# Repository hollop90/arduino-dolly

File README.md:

# Arduino Dolly

A clone of the Arduino Nano, but a little different.

## Overview Image

## Schematic

## 3D PCB

## Copper Layers

## todos

- [X] calculate crystal values
  - [X] calculate load capacitors - 12pf
  - [X] inspect layout - seems fine
- [X] Research USB TVS diodes
  - [X] the ones i'm using are probably not appropriate - yeah they are for RS485. FIXED
  - [X] look into what phils lab uses or the CATS board
- [X] Look into controlled impedance traces. NOT NEEDED
  - [X] calculate for the USB port. NOT DONE
- [X] Double check USB C layout
  - [X] ground the shilding
  - [X] series termination reistors? NAH
- [X] double check vreg capacitors. NEXT TIME USE 10u ON BOTH SIDES
- [X] check all capacitor dielectrics
- [X] add a fuse?. NO
- [X] review voltage selector diode. LGTM
- [X] Make a final BOM
- [X] Make production files
- [ ] Rip up traces and try alternete routing for MCU
- [X] CP2102 and others, what to do with unused pins

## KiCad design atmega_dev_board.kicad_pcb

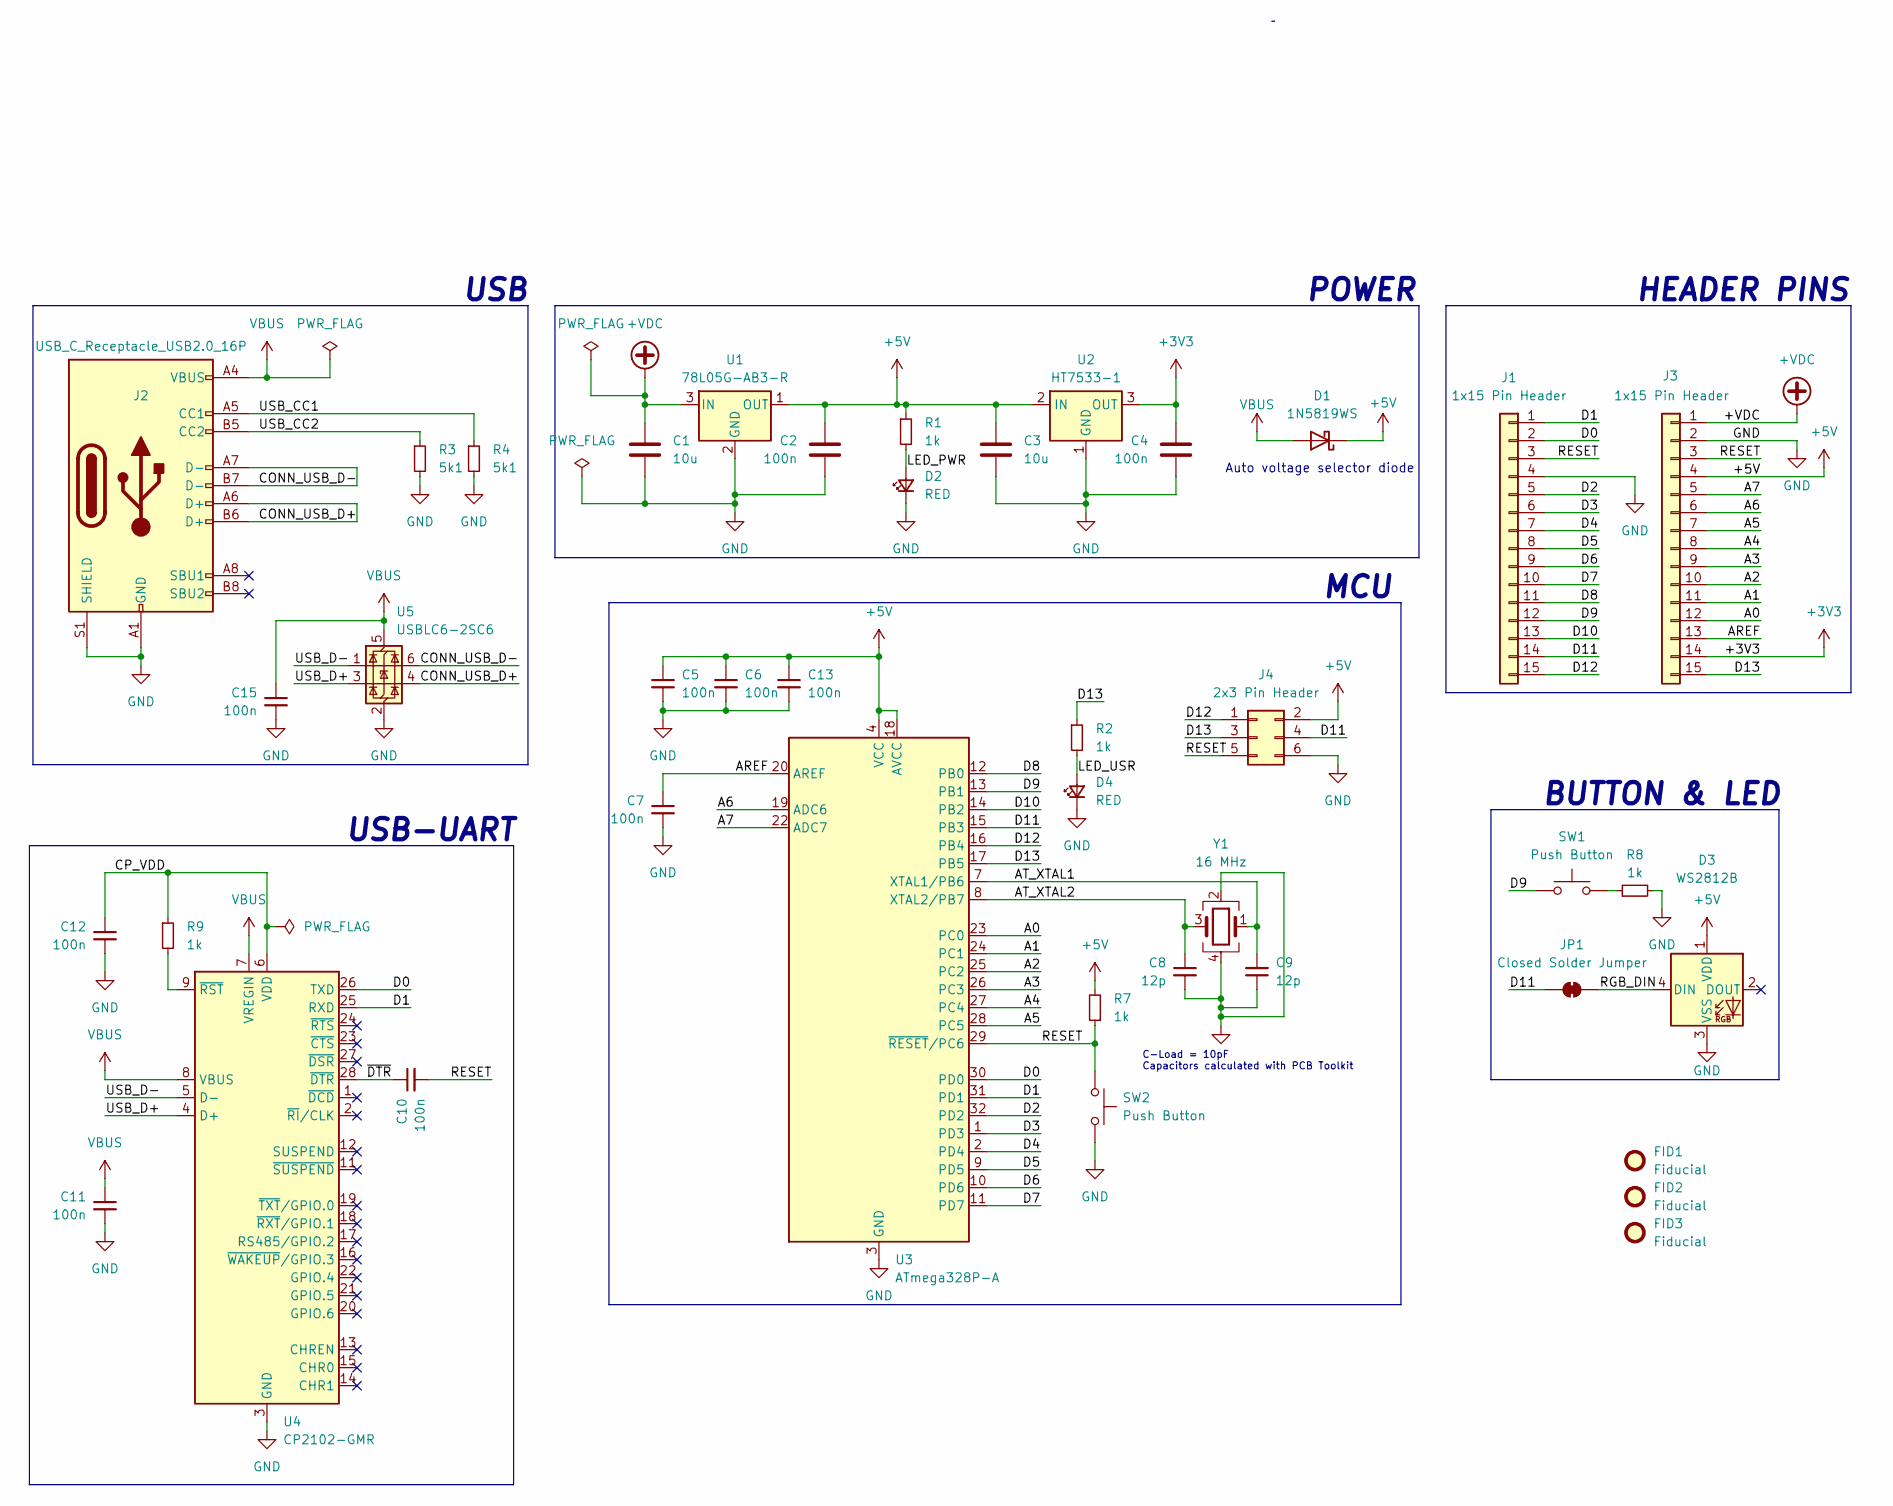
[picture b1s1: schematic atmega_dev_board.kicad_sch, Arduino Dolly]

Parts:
C1, C3: 10u; C_0603_1608Metric; Manufacturer Part# CL10A106KP8NNNC; JLCPCB Part # C19702
C2, C4, C5, C6, C7, C10, C11, C12, C13, C15: 100n; C_0603_1608Metric; Manufacturer Part# CC0603KRX7R9BB104; JLCPCB Part # C14663
C8, C9: 12p; C_0603_1608Metric; Manufacturer Part# CL10C120JB8NNNC; JLCPCB Part # C38523
D1: 1N5819WS; D_SOD-323; Manufacturer Part# 1N5819WS; JLCPCB Part # C191023
D2, D4: RED; LED_0603_1608Metric; Manufacturer Part# KT-0603R; JLCPCB Part # C2286
D3: WS2812B; LED_WS2812B_PLCC4_5.0x5.0mm_P3.2mm; Manufacturer Part# XL-5050RGBC-WS2812B; JLCPCB Part # C2843785
FID1, FID2, FID3: Fiducial; Fiducial_0.5mm_Mask1mm
J1, J3: 1x15 Pin Header; PinHeader_1x15_P2.54mm_Vertical
J2: USB_C_Receptacle_USB2.0_16P; USB_C_Receptacle_GCT_USB4105-xx-A_16P_TopMnt_Horizontal; Manufacturer Part# XUBF-0336-0817B; JLCPCB Part # C7527694
J4: 2x3 Pin Header; PinHeader_2x03_P2.54mm_Vertical
JP1: Closed Solder Jumper; SolderJumper-2_P1.3mm_Bridged_RoundedPad1.0x1.5mm
R1, R2, R7, R8, R9: 1k; R_0603_1608Metric; Manufacturer Part# 0603WAF1001T5E; JLCPCB Part # C21190
R3, R4: 5k1; R_0603_1608Metric; Manufacturer Part# 0603WAF5101T5E; JLCPCB Part # C23186
SW1, SW2: Push Button; SW_SPST_TL3342; Manufacturer Part# TS-1187A-B-A-B; JLCPCB Part # C318884
U1: 78L05G-AB3-R; SOT-89-3; Manufacturer Part# 78L05G-AB3-R; JLCPCB Part # C71136
U2: HT7533-1; SOT-89-3; Manufacturer Part# HT7533-1; JLCPCB Part # C14289
U3: ATmega328P-A; TQFP-32_7x7mm_P0.8mm; Manufacturer Part# ATMEGA328P-AU; JLCPCB Part # C14877
U4: CP2102-GMR; QFN-28-1EP_5x5mm_P0.5mm_EP3.35x3.35mm; Manufacturer Part# CP2102-GMR; JLCPCB Part # C6568
U5: USBLC6-2SC6; SOT-23-6
Y1: 16 MHz; Crystal_SMD_3225-4Pin_3.2x2.5mm; Manufacturer Part# X322516MLB4SI; JLCPCB Part # C13738

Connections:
+3V3: C4.1, J3.14, U2.3 (OUT)
+5V: C2.1, C3.1, C5.1, C6.1, C13.1, D1.1 (K), D3.1 (VDD), J3.4, J4.2, R1.1, R7.2, U1.1 (OUT), U2.2 (IN), U3.4 (VCC), U3.6 (VCC), U3.18 (AVCC)
+VDC: C1.1, J3.1, U1.3 (IN)
/A0: J3.12, U3.23 (PC0)
/A1: J3.11, U3.24 (PC1)
/A2: J3.10, U3.25 (PC2)
/A3: J3.9, U3.26 (PC3)
/A4: J3.8, U3.27 (PC4)
/A5: J3.7, U3.28 (PC5)
/A6: J3.6, U3.19 (ADC6)
/A7: J3.5, U3.22 (ADC7)
/AREF: C7.1, J3.13, U3.20 (AREF)
/AT_XTAL1: C9.2, U3.7 (XTAL1/PB6), Y1.1
/AT_XTAL2: C8.1, U3.8 (XTAL2/PB7), Y1.3
/CONN_USB_D+: J2.A6 (D+), J2.B6 (D+), U5.4 (I/O2)
/CONN_USB_D-: J2.A7 (D-), J2.B7 (D-), U5.6 (I/O1)
/CP_VDD: C12.1, R9.1, U4.6 (VDD)
/D0: J1.2, U3.30 (PD0), U4.26 (TXD)
/D1: J1.1, U3.31 (PD1), U4.25 (RXD)
/D2: J1.5, U3.32 (PD2)
/D3: J1.6, U3.1 (PD3)
/D4: J1.7, U3.2 (PD4)
/D5: J1.8, U3.9 (PD5)
/D6: J1.9, U3.10 (PD6)
/D7: J1.10, U3.11 (PD7)
/D8: J1.11, U3.12 (PB0)
/D9: J1.12, SW1.1, U3.13 (PB1)
/D10: J1.13, U3.14 (PB2)
/D11: J1.14, J4.4, JP1.1 (A), U3.15 (PB3)
/D12: J1.15, J4.1, U3.16 (PB4)
/D13: J3.15, J4.3, R2.1, U3.17 (PB5)
/LED_PWR: D2.2 (A), R1.2
/LED_USR: D4.2 (A), R2.2
/RESET: C10.2, J1.3, J3.3, J4.5, R7.1, SW2.1, U3.29 (~RESET/PC6)
/RGB_DIN: D3.4 (DIN), JP1.2 (B)
/USB_CC1: J2.A5 (CC1), R4.1
/USB_CC2: J2.B5 (CC2), R3.1
/USB_D+: U4.4 (D+), U5.3 (I/O2)
/USB_D-: U4.5 (D-), U5.1 (I/O1)
/~DTR: C10.1, U4.28 (~DTR)
GND: C1.2, C2.2, C3.2, C4.2, C5.2, C6.2, C7.2, C8.2, C9.1, C11.2, C12.2, C13.2, C15.2, D2.1 (K), D3.3 (VSS), D4.1 (K), J1.4, J2.A1 (GND), J2.A12 (GND), J2.B1 (GND), J2.B12 (GND), J2.S1 (SHIELD), J3.2, J4.6, R3.2, R4.2, R8.2, SW2.2, U1.2 (GND), U2.1 (GND), U3.3 (GND), U3.5 (GND), U3.21 (GND), U4.3 (GND), U4.29 (GND), U5.2 (GND), Y1.2, Y1.4
unnamed: R8.1, SW1.2
unnamed: R9.2, U4.9 (~RST)
VBUS: C11.1, C15.1, D1.2 (A), J2.A4 (VBUS), J2.A9 (VBUS), J2.B4 (VBUS), J2.B9 (VBUS), U4.7 (VREGIN), U4.8 (VBUS), U5.5 (VBUS)

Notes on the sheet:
Auto voltage selector diode
MCU
POWER
HEADER PINS
C-Load = 10pF Capacitors calculated with PCB Toolkit
USB
BUTTON & LED
USB-UART

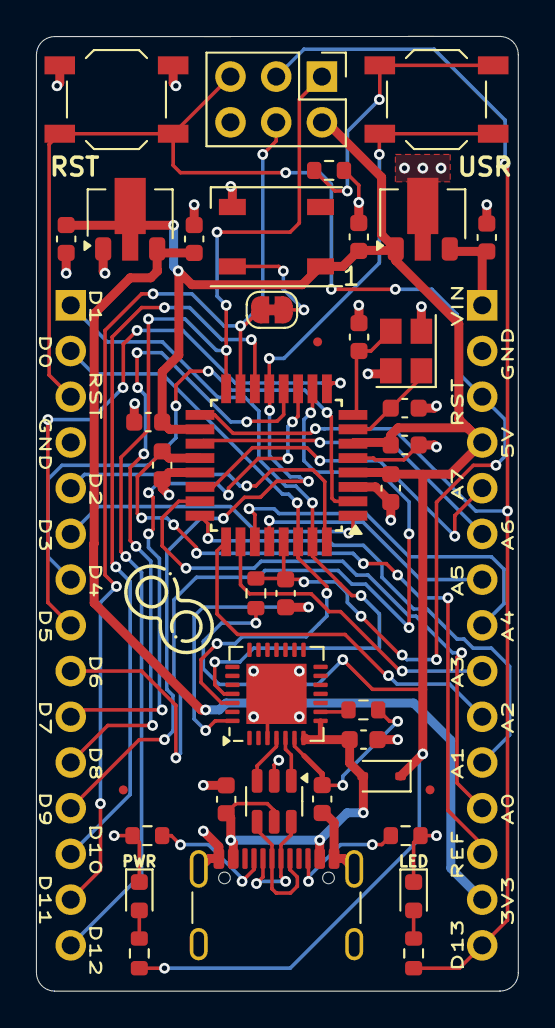
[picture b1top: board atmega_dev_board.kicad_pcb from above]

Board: 4 copper layers, 26.8 x 53.0 mm, 41 parts (0 on the bottom side), 44 nets.

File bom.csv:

"Reference","Value","Datasheet","Footprint","Qty","DNP","Description","JLCPCB Part #"
"J2","USB_C_Receptacle_USB2.0_16P","https://wmsc.lcsc.com/wmsc/upload/file/pdf/v2/lcsc/230918181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","Connector_USB:USB_C_Receptacle_GCT_USB4105-xx-A_16P_TopMnt_Horizontal","1","","USB 2.0-only 16P Type-C Receptacle connector","C7527694"
"D3","WS2812B","https://wmsc.lcsc.com/wmsc/upload/file/pdf/v2/lcsc/240412094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","LED_SMD:LED_WS2812B_PLCC4_5.0x5.0mm_P3.2mm","1","","RGB LED with integrated controller","C2843785"
"SW1,SW2","Push Button","https://wmsc.lcsc.com/wmsc/upload/file/pdf/v2/lcsc/230414003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","Button_Switch_SMD:SW_SPST_TL3342","2","","Push button switch, generic, two pins","C318884"
"D1","1N5819WS","https://wmsc.lcsc.com/wmsc/upload/file/pdf/v2/lcsc/220428143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","Diode_SMD:D_SOD-323","1","","Schottky diode","C191023"
"U1","78L05G-AB3-R","https://wmsc.lcsc.com/wmsc/upload/file/pdf/v2/lcsc/230414003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","Package_TO_SOT_SMD:SOT-89-3","1","","Positive 100mA 30V Linear Regulator, Fixed Output 5V, SOT-89","C71136"
"C8,C9","12p","https://wmsc.lcsc.com/wmsc/upload/file/pdf/v2/lcsc/230414003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","Capacitor_SMD:C_0603_1608Metric","2","","Unpolarized capacitor, small symbol","C38523"
"R3,R4","5k1","https://wmsc.lcsc.com/wmsc/upload/file/pdf/v2/lcsc/220601011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","Resistor_SMD:R_0603_1608Metric","2","","Resistor, small symbol","C23186"
"R1,R2,R7,R8,R9","1k","https://wmsc.lcsc.com/wmsc/upload/file/pdf/v2/lcsc/220601013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","Resistor_SMD:R_0603_1608Metric","5","","Resistor, small symbol","C21190"
"C1,C3","10u","https://wmsc.lcsc.com/wmsc/upload/file/pdf/v2/lcsc/230414003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","Capacitor_SMD:C_0603_1608Metric","2","","Unpolarized capacitor","C19702"
"U3","ATmega328P-A","http://ww1.microchip.com/downloads/en/DeviceDoc/ATmega328_P%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","Package_QFP:TQFP-32_7x7mm_P0.8mm","1","","20MHz, 32kB Flash, 2kB SRAM, 1kB EEPROM, TQFP-32","C14877"
"C2,C4,C5,C6,C7,C10,C11,C12,C13,C15","100n","https://wmsc.lcsc.com/wmsc/upload/file/pdf/v2/lcsc/221110170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","Capacitor_SMD:C_0603_1608Metric","10","","-- mixed values --","C14663"
"U2","HT7533-1","https://wmsc.lcsc.com/wmsc/upload/file/pdf/v2/lcsc/231219111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","Package_TO_SOT_SMD:SOT-89-3","1","","Positive 100mA 30V Linear Regulator, Fixed Output 3.3V, SOT-89","C14289"
"Y1","16 MHz","https://wmsc.lcsc.com/wmsc/upload/file/pdf/v2/lcsc/240329150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","Crystal:Crystal_SMD_3225-4Pin_3.2x2.5mm","1","","Four pin crystal, GND on pins 2 and 4","C13738"
"U4","CP2102-GMR","https://wmsc.lcsc.com/wmsc/upload/file/pdf/v2/lcsc/181108192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","Package_DFN_QFN:QFN-28-1EP_5x5mm_P0.5mm_EP3.35x3.35mm","1","","USB to UART master bridge, QFN-28","C6568"
"D2,D4","RED","https://wmsc.lcsc.com/wmsc/upload/file/pdf/v2/lcsc/181023111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","LED_SMD:LED_0603_1608Metric","2","","Light emitting diode, small symbol","C2286"
"U5","USBLC6-2SC6","https://www.st.com/resource/en/datasheet/usblc6-2.pdf","Package_TO_SOT_SMD:SOT-23-6","1","","Very low capacitance ESD protection diode, 2 data-line, SOT-23-6",""
"J4","2x3 Pin Header","~","Connector_PinHeader_2.54mm:PinHeader_2x03_P2.54mm_Vertical","1","","Generic connector, double row, 02x03, counter clockwise pin numbering scheme (similar to DIP package numbering), script generated (kicad-library-utils/schlib/autogen/connector/)",""
"J1,J3","1x15 Pin Header","~","Connector_PinHeader_2.54mm:PinHeader_1x15_P2.54mm_Vertical","2","","Generic connector, single row, 01x15, script generated (kicad-library-utils/schlib/autogen/connector/)",""

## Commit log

2024-05-26 init commit
2024-05-26 Replace op-amps with a diode
2024-05-26 Replace voltage regulators with 78XXs
2024-05-27 Move to USB C and CP2102
2024-05-28 Adjust pin header and board size to match 0m1" pitch
2024-05-28 New placements of PCB
2024-05-28 Tidy up schema and route all but GPIO traces
2024-05-29 Update PCB meta data. More GPIO routing
2024-06-02 Finish routing, update design rules
2024-06-02 Add README and image
2024-06-02 Update revision number and date
2024-06-03 Update loading cap values (from 22p to 12p)
2024-06-03 Swap out TVS diodes. Ground USB shield
2024-06-03 Update BOM and component values
2024-06-04 lots
    Sch: Add feducials
    PCB: Add pin labels to silkscreen
2024-06-04 Add pull up R to RESET. Add current limiting R to USR button
2024-06-05 Finishing touches
    ## PCB
    * Tighten zone clearance from 0.5 to 0.2
    * Add silkscreen (names and logos)
    * Reposition LEDs
    * Round corners
    * Remove unecessaary components
2024-06-05 Fix via sizing and other small changes
    * Update part numbers
    * Update BOM
    * Slight fixes to schematic
2024-06-09 Update BOM
2024-06-09 Add more images to readme
2024-06-09 Added todo list
2024-06-25 fix: Fix UART mis-match. Fix VREG footprint
2024-09-23 fix: Update schematic svg to reflect project changes
